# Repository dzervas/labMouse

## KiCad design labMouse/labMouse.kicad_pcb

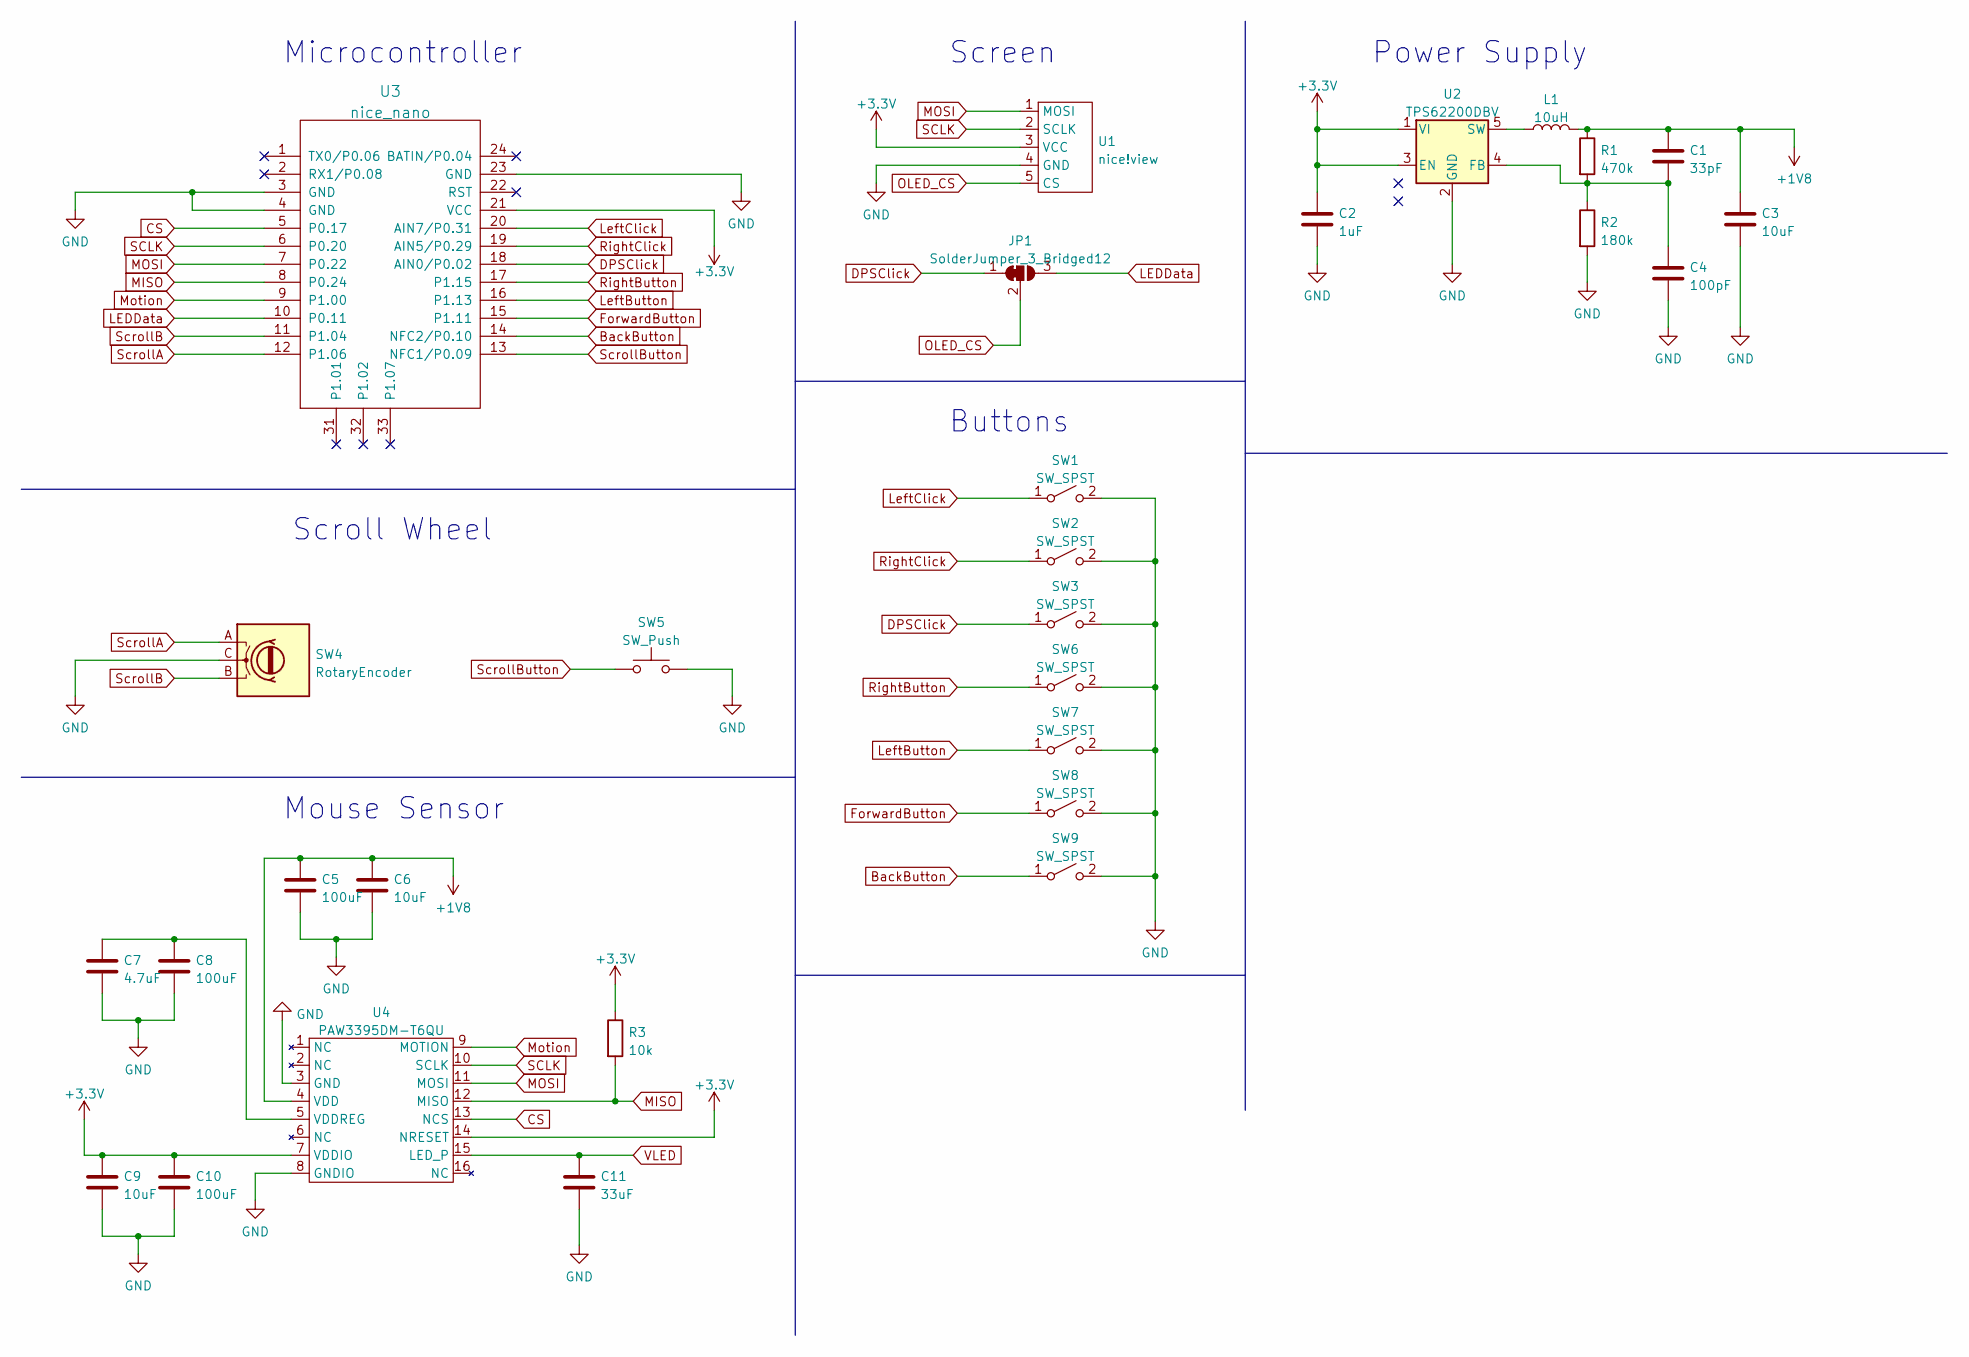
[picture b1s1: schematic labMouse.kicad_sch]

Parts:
C1: 33pF; C_1206_3216Metric_Pad1.33x1.80mm_HandSolder
C2: 1uF; C_1206_3216Metric_Pad1.33x1.80mm_HandSolder
C3, C6, C9: 10uF; C_1206_3216Metric_Pad1.33x1.80mm_HandSolder
C4: 100pF; C_1206_3216Metric_Pad1.33x1.80mm_HandSolder
C5, C8, C10: 100uF; C_1206_3216Metric_Pad1.33x1.80mm_HandSolder
C7: 4.7uF; C_1206_3216Metric_Pad1.33x1.80mm_HandSolder
C11: 33uF; C_1206_3216Metric_Pad1.33x1.80mm_HandSolder
JP1: SolderJumper_3_Bridged12; SolderJumper-3_P1.3mm_Bridged12_RoundedPad1.0x1.5mm_NumberL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
L1: 10uH; L_1210_3225Metric_Pad1.42x2.65mm_HandSolder
R1: 470k; R_1206_3216Metric_Pad1.30x1.75mm_HandSolder
R2: 180k; R_1206_3216Metric_Pad1.30x1.75mm_HandSolder
R3: 10k; R_1206_3216Metric_Pad1.30x1.75mm_HandSolder
SW1, SW2, SW3, SW6, SW7, SW8, SW9: SW_SPST; PinHeader_1x02_P2.54mm_Vertical
SW4: RotaryEncoder; Japanese_Alps_Encoder_EC10E1220501
SW5: SW_Push; PinHeader_1x02_P2.54mm_Vertical
U1: nice!view
U2: TPS62200DBV; SOT-23-5
U3: nice_nano
U4: PAW3395DM-T6QU

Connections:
+1V8: C1.1, C3.1, C5.1, C6.1, L1.2, R1.1, U4.4 (VDD)
+3.3V: C2.1, C9.1, C10.1, R3.1, U1.3 (VCC), U2.1 (VI), U2.3 (EN), U3.21 (VCC), U4.7 (VDDIO), U4.14 (NRESET)
BackButton: SW9.1 (A), U3.14 (NFC2/P0.10)
CS: U3.5 (P0.17), U4.13 (NCS)
DPSClick: JP1.1 (A), SW3.1 (A), U3.18 (AIN0/P0.02)
ForwardButton: SW8.1 (A), U3.15 (P1.11)
GND: C2.2, C3.2, C4.2, C5.2, C6.2, C7.2, C8.2, C9.2, C10.2, C11.2, R2.2, SW1.2 (B), SW2.2 (B), SW3.2 (B), SW4.C, SW5.2, SW6.2 (B), SW7.2 (B), SW8.2 (B), SW9.2 (B), U1.4 (GND), U2.2 (GND), U3.3 (GND), U3.4 (GND), U3.23 (GND), U4.3 (GND), U4.8 (GNDIO)
LEDData: JP1.3 (B), U3.10 (P0.11)
LeftButton: SW7.1 (A), U3.16 (P1.13)
LeftClick: SW1.1 (A), U3.20 (AIN7/P0.31)
MISO: R3.2, U3.8 (P0.24), U4.12 (MISO)
MOSI: U1.1 (MOSI), U3.7 (P0.22), U4.11 (MOSI)
Motion: U3.9 (P1.00), U4.9 (MOTION)
unnamed: C7.1, C8.1, U4.5 (VDDREG)
unnamed: L1.1, U2.5 (SW)
unnamed: C1.2, C4.1, R1.2, R2.1, U2.4 (FB)
OLED_CS: JP1.2 (C), U1.5 (CS)
RightButton: SW6.1 (A), U3.17 (P1.15)
RightClick: SW2.1 (A), U3.19 (AIN5/P0.29)
SCLK: U1.2 (SCLK), U3.6 (P0.20), U4.10 (SCLK)
ScrollA: SW4.A, U3.12 (P1.06)
ScrollB: SW4.B, U3.11 (P1.04)
ScrollButton: SW5.1, U3.13 (NFC1/P0.09)
VLED: C11.1, U4.15 (LED_P)

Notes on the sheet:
Scroll Wheel
Buttons
Power Supply
Mouse Sensor
Microcontroller
Screen

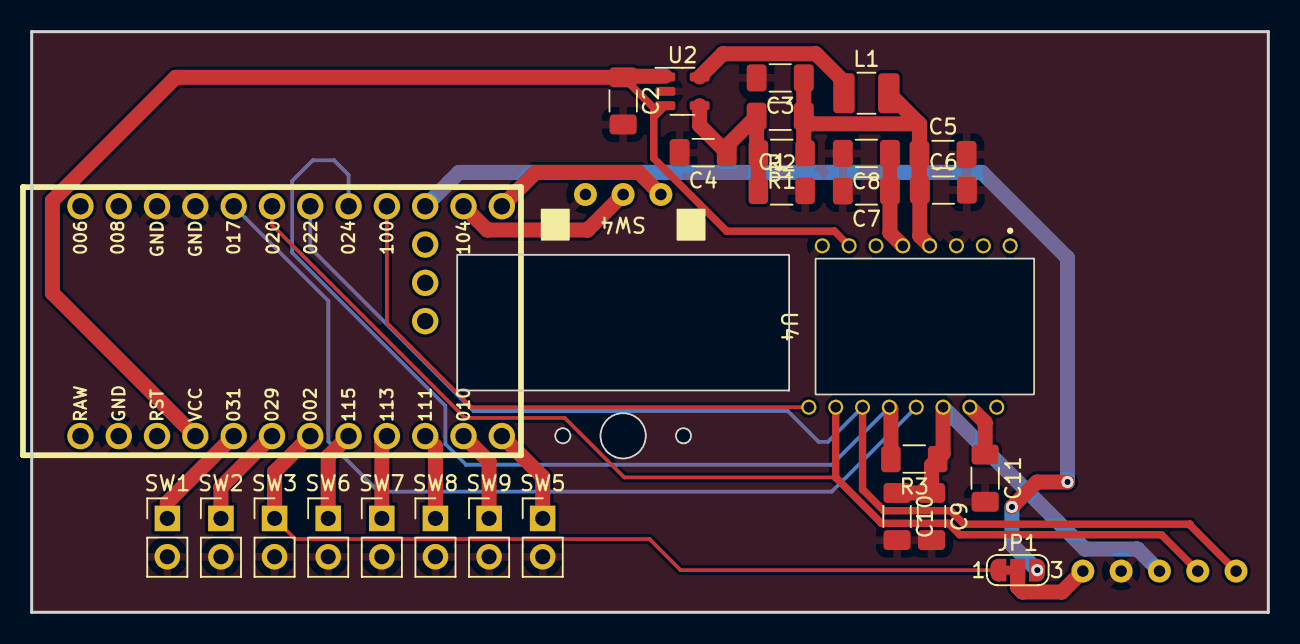
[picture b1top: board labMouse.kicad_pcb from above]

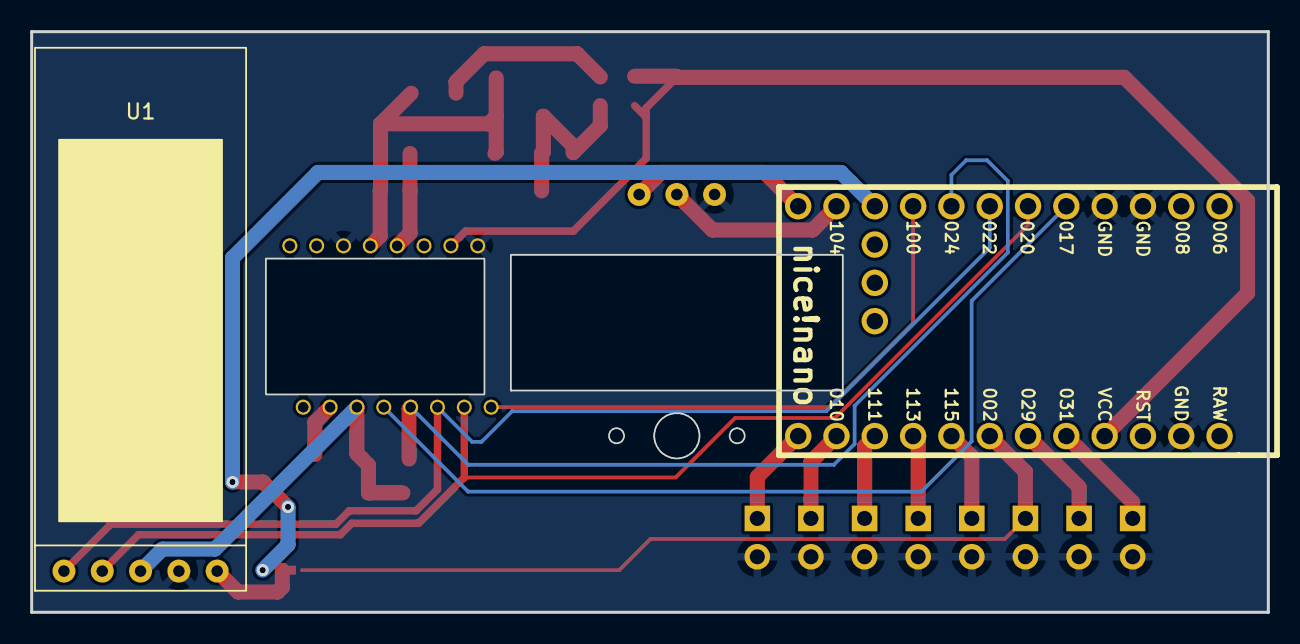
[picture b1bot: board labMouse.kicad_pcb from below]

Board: 2 copper layers, 82.0 x 38.5 mm, 29 parts (2 on the bottom side), 24 nets.

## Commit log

2023-01-09 Test FreeCAD git
2023-01-10 Made half the shell face!
2023-01-10 Made the whole solid
2023-01-11 Change 3D Model compression in FreeCAD
2023-01-11 Remove the 3D model to readd it
2023-01-11 Readd 3D model
2023-01-12 Raise the eyebrow of the shell
2023-01-12 Fix artifact in mirrored half object of shell
2023-01-12 Create the base surfaces
2023-01-13 Make the body a solid
2023-01-13 Remove super old blender try
2023-01-13 Playin around with the body's top surface
2023-01-16 Start the base shell
2023-01-18 Roughly finish the body
2023-01-18 Add the two parts in an assembly
2023-01-19 In the middle of changing the gordon surface to filled curves
2023-01-19 Create the first schematic with the custom symbols and footprints
2023-01-19 [schematic] Add screen and power supply
2023-01-19 [schematic] Raise the power supply current limit to 60mA
2023-01-21 Create first PCB
2023-01-23 First 3D model of the encoder
2023-06-18 No idea
